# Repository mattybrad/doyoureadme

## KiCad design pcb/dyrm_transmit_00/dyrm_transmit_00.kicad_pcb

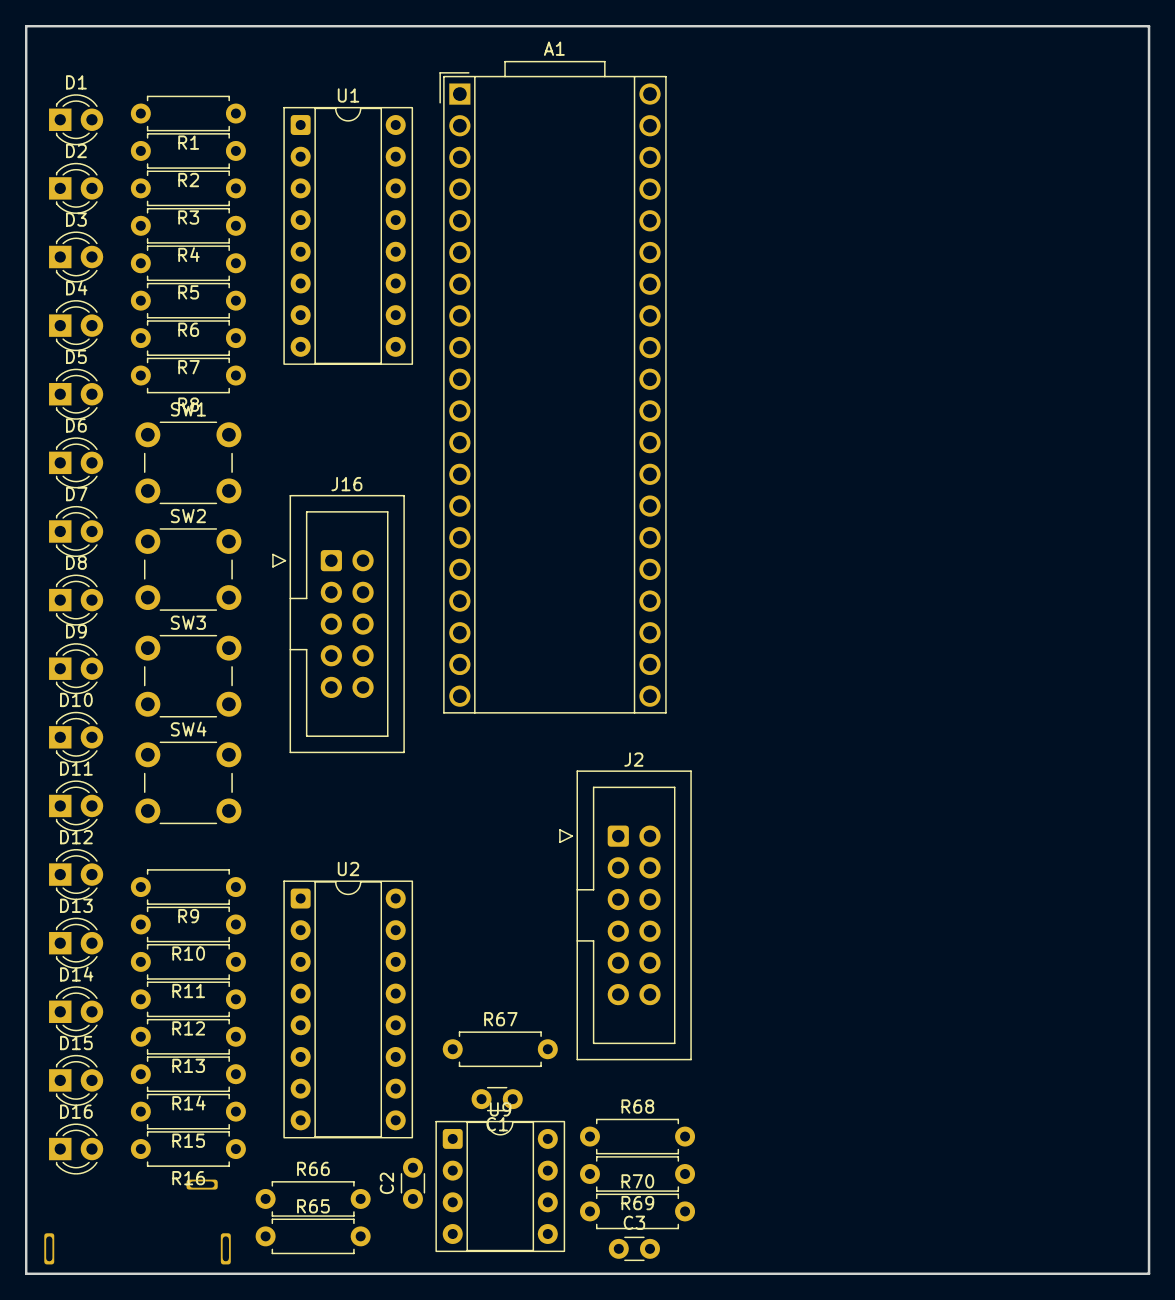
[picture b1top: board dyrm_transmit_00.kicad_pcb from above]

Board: 2 copper layers, 90.0 x 100.0 mm, 52 parts (1 on the bottom side), 58 nets, no tracks yet.

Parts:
A1: Electrosmith_Daisy_Seed_Rev4; Electrosmith_Daisy_Seed
C1: 100nF; C_Disc_D3.0mm_W1.6mm_P2.50mm
C2, C3: 330pF; C_Disc_D3.0mm_W1.6mm_P2.50mm
D1, D2, D3, D4, D5, D6, D7, D8, D9, D10, D11, D12, D13, D14, D15, D16: LED; LED_D3.0mm
J1: Euro_Audio_Input; Jack_3.5mm_WQP729JH_Horizontal
J2: Conn_02x06_Counter_Clockwise; IDC-Header_2x06_P2.54mm_Vertical
J16: Eurorack_Power; IDC-Header_2x05_P2.54mm_Vertical
R1, R2, R3, R4, R5, R6, R7, R8, R9, R10, R11, R12, R13, R14, R15, R16: R_US; R_Axial_DIN0207_L6.3mm_D2.5mm_P7.62mm_Horizontal
R65, R70: 100k; R_Axial_DIN0207_L6.3mm_D2.5mm_P7.62mm_Horizontal
R66, R69: 10k; R_Axial_DIN0207_L6.3mm_D2.5mm_P7.62mm_Horizontal
R67, R68: 100R; R_Axial_DIN0207_L6.3mm_D2.5mm_P7.62mm_Horizontal
SW1, SW2, SW3, SW4: SW_Push; SW_PUSH_6mm
U1, U2: 74HC595; DIP-16_W7.62mm_Socket
U9: TL072; DIP-8_W7.62mm_Socket

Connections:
+3.3V: J2.2, U1.10 (~SRCLR), U1.16 (VCC), U2.10 (~SRCLR), U2.16 (VCC)
+12V: A1.39 (VIN), C1.1, J16.9, J16.10, U9.8 (V+)
-12V: C1.2, J16.1, J16.2, U9.4 (V-)
BUTTON_1: A1.31 (SAI2_MCLK), SW1.1
BUTTON_2: A1.32 (SAI2_SD_B), SW2.1
BUTTON_3: A1.33 (SAI2_SD_A), SW3.1
BUTTON_4: A1.34 (SAI2_FS), SW4.1
CODEC_INPUT_1: A1.16 (AUDIO_IN_1), R67.2
CODEC_OUTPUT_1: A1.18 (AUDIO_OUT_1), R69.1
EURO_AUDIO_OUTPUT: J2.8, R68.2
GND: A1.20 (AGND), A1.40 (DGND), D1.1 (K), D2.1 (K), D3.1 (K), D4.1 (K), D5.1 (K), D6.1 (K), D7.1 (K), D8.1 (K), D9.1 (K), D10.1 (K), D11.1 (K), D12.1 (K), D13.1 (K), D14.1 (K), D15.1 (K), D16.1 (K), J1.S, J1.TN, J2.1, J16.3, J16.4, J16.5, J16.6, J16.7, J16.8, SW1.2, SW2.2, SW3.2, SW4.2, U1.8 (GND), U1.13 (~OE), U2.8 (GND), U2.13 (~OE), U9.3 (+), U9.5 (+)
IR_CLOCK: A1.5 (SD_DATA_0), U1.11 (SRCLK), U2.11 (SRCLK)
IR_DATA: A1.3 (SD_DATA_2), U1.14 (SER)
IR_LATCH: A1.4 (SD_DATA_1), U1.12 (RCLK), U2.12 (RCLK)
MUX_ADDRESS_A: A1.26 (ADC_4), J2.3
MUX_ADDRESS_B: A1.27 (ADC_5), J2.4
unnamed: C2.2, R66.2, R67.1, U9.1
unnamed: C3.2, R68.1, R70.2, U9.7
unnamed: D1.2 (A), R1.2
unnamed: D2.2 (A), R2.2
unnamed: D3.2 (A), R3.2
unnamed: D4.2 (A), R4.2
unnamed: D5.2 (A), R5.2
unnamed: D6.2 (A), R6.2
unnamed: D7.2 (A), R7.2
unnamed: D8.2 (A), R8.2
unnamed: D9.2 (A), R9.2
unnamed: D10.2 (A), R10.2
unnamed: D11.2 (A), R11.2
unnamed: D12.2 (A), R12.2
unnamed: D13.2 (A), R13.2
unnamed: D14.2 (A), R14.2
unnamed: D15.2 (A), R15.2
unnamed: D16.2 (A), R16.2
unnamed: J1.T, R65.1
unnamed: R1.1, U1.15 (QA)
unnamed: R2.1, U1.1 (QB)
unnamed: R3.1, U1.2 (QC)
unnamed: R4.1, U1.3 (QD)
unnamed: R5.1, U1.4 (QE)
unnamed: R6.1, U1.5 (QF)
unnamed: R7.1, U1.6 (QG)
unnamed: U1.9 (QH'), U2.14 (SER)
unnamed: R8.1, U1.7 (QH)
unnamed: R9.1, U2.15 (QA)
unnamed: R10.1, U2.1 (QB)
unnamed: R11.1, U2.2 (QC)
unnamed: R12.1, U2.3 (QD)
unnamed: R13.1, U2.4 (QE)
unnamed: R14.1, U2.5 (QF)
unnamed: R15.1, U2.6 (QG)
unnamed: R16.1, U2.7 (QH)
unnamed: C2.1, R65.2, R66.1, U9.2 (-)
unnamed: C3.1, R69.2, R70.1, U9.6 (-)
PHOTODIODE_GROUP_1X: A1.22 (ADC_0), J2.12
PHOTODIODE_GROUP_1Y: A1.23 (ADC_1), J2.11
PHOTODIODE_GROUP_2X: A1.24 (ADC_2), J2.10
PHOTODIODE_GROUP_2Y: A1.25 (ADC_3), J2.9

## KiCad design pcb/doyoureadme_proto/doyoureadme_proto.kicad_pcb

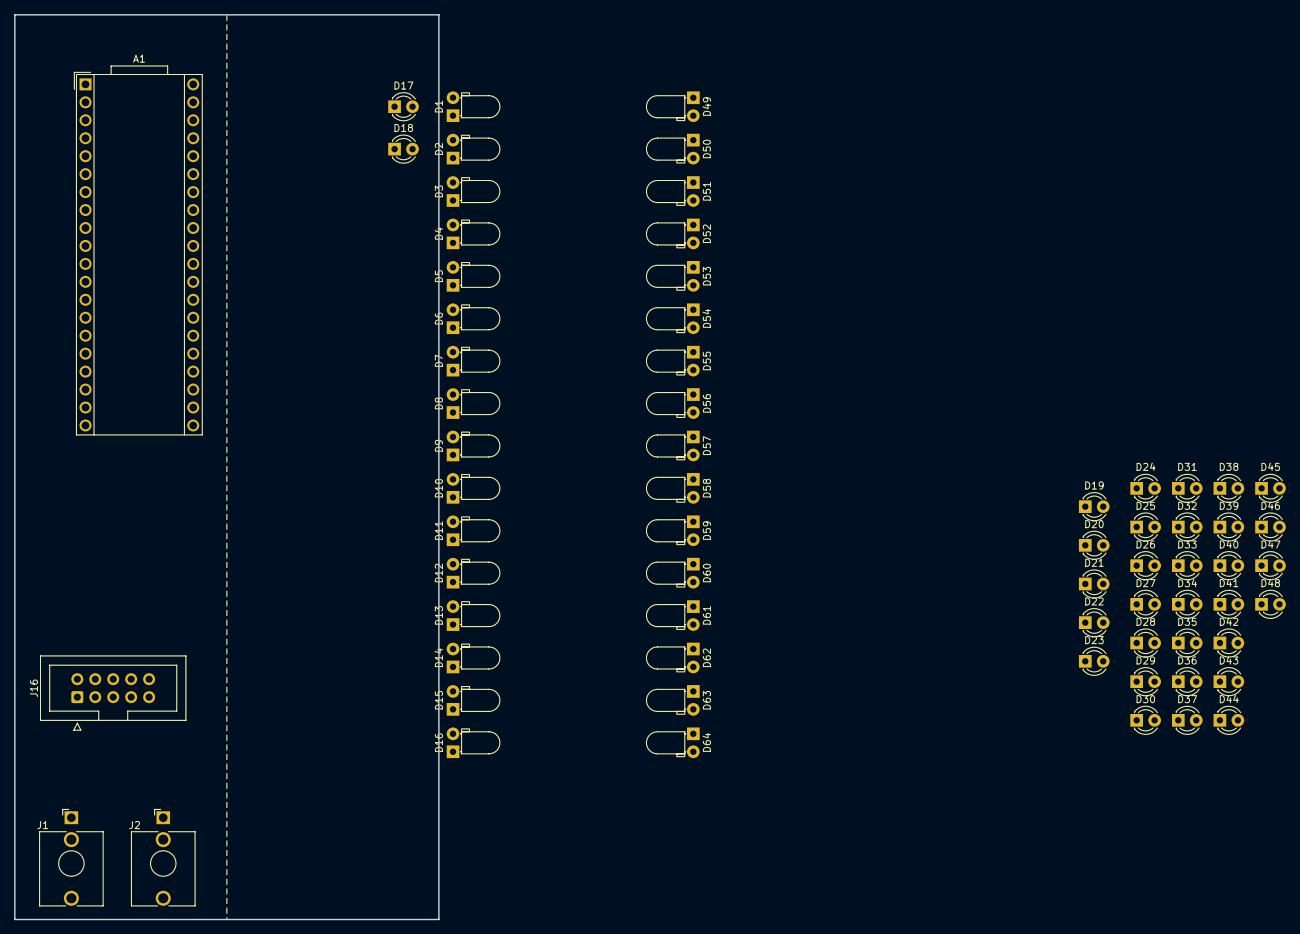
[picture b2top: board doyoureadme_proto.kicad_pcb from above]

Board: 2 copper layers, 60.0 x 128.0 mm, 68 parts (0 on the bottom side), 4 nets, no tracks yet.

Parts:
A1: Electrosmith_Daisy_Seed_Rev4; Electrosmith_Daisy_Seed
D1, D2, D3, D4, D5, D6, D7, D8, D9, D10, D11, D12, D13, D14, D15, D16: LED; LED_D3.0mm_Horizontal_O1.27mm_Z2.0mm
D17, D18, D19, D20, D21, D22, D23, D24, D25, D26, D27, D28, D29, D30, D31, D32, D33, D34, D35, D36, D37, D38, D39, D40, D41, D42, D43, D44, D45, D46, D47, D48: LED; LED_D3.0mm
D49, D50, D51, D52, D53, D54, D55, D56, D57, D58, D59, D60, D61, D62, D63, D64: D_Photo; LED_D3.0mm_Horizontal_O1.27mm_Z2.0mm
J1: Euro_Audio_Input; Jack_3.5mm_QingPu_WQP-PJ398SM_Vertical_CircularHoles
J2: Euro_Audio_Output; Jack_3.5mm_QingPu_WQP-PJ398SM_Vertical_CircularHoles
J16: Eurorack_Power; IDC-Header_2x05_P2.54mm_Vertical

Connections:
+3.3V: D49.1 (K), D50.1 (K), D51.1 (K), D52.1 (K), D53.1 (K), D54.1 (K), D55.1 (K), D56.1 (K), D57.1 (K), D58.1 (K), D59.1 (K), D60.1 (K), D61.1 (K), D62.1 (K), D63.1 (K), D64.1 (K)
+12V: A1.39 (VIN), J16.9, J16.10
-12V: J16.1, J16.2
GND: A1.20 (AGND), A1.40 (DGND), J1.S, J1.TN, J16.3, J16.4, J16.5, J16.6, J16.7, J16.8
